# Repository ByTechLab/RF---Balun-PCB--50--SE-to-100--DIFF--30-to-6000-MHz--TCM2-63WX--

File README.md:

<div align="center">
    
</div>

Mini Circuits TCM2-63WX+ based balun PCB.

### Read more at BYTECHLAB:

<table style="width: 100%; border: none;" cellspacing="0" cellpadding="0" border="0">
  <tr>
    <td></td>
    <td>https://bytechlab.com/2025/07/balun-pcb-tcm2-63wx/</td>
  </tr>
</table>

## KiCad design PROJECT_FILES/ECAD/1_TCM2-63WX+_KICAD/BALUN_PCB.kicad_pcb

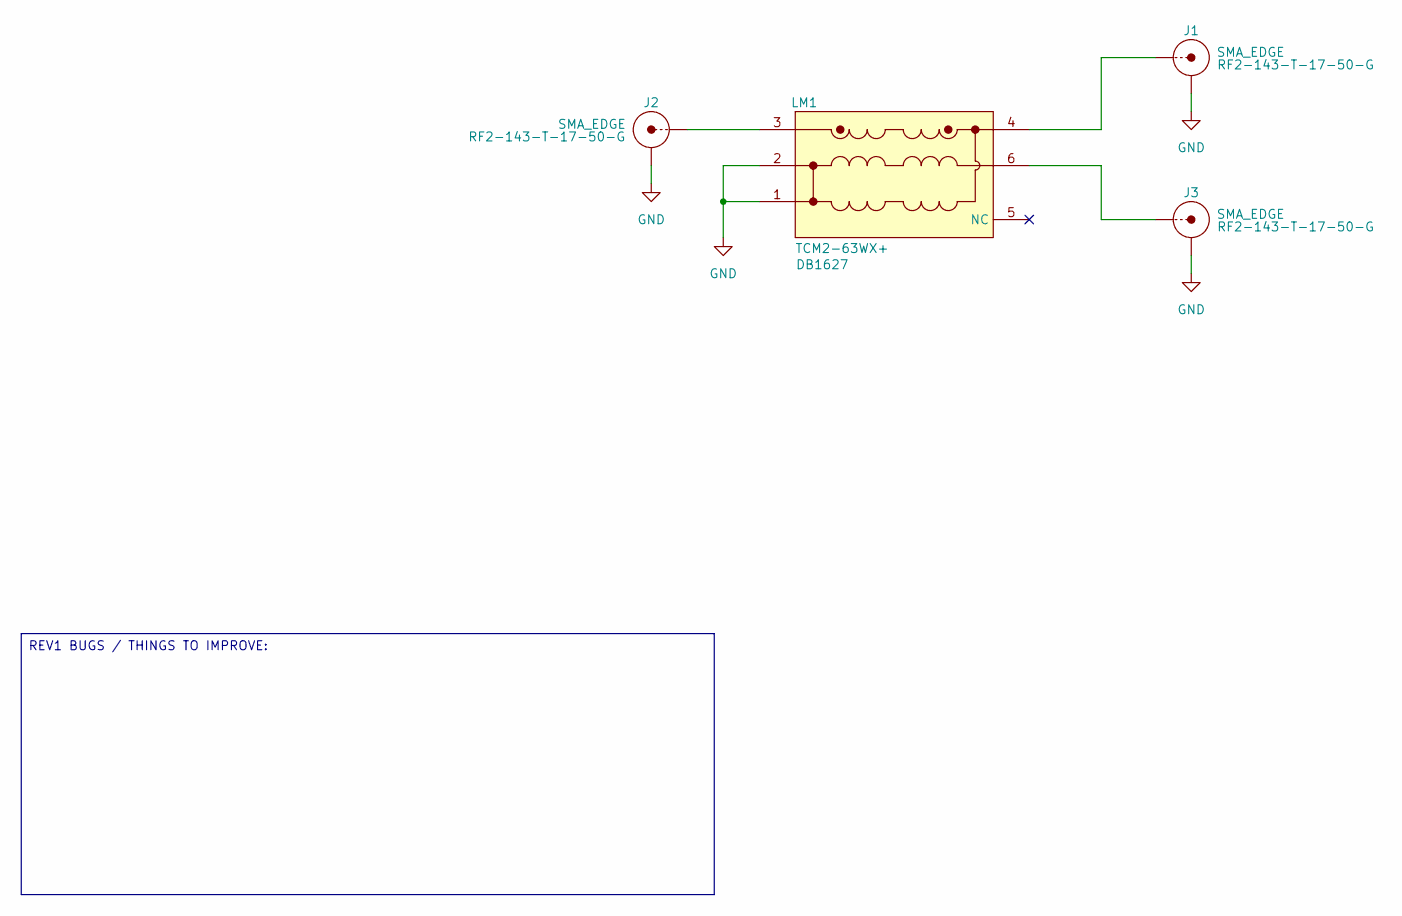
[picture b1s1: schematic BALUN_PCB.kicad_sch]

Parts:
J1, J2, J3: J_RF2-143-T-17-50-G; Manufacturer Part Number RF2-143-T-17-50-G
LM1: LM_TCM2-63WX+; Manufacturer Part Number TCM2-63WX+

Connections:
GND: J1.2 (GND), J2.2 (GND), J3.2 (GND), LM1.1, LM1.2
unnamed: J1.1 (SIG), LM1.4
unnamed: J2.1 (SIG), LM1.3
unnamed: J3.1 (SIG), LM1.6

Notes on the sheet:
REV1 BUGS / THINGS TO IMPROVE:

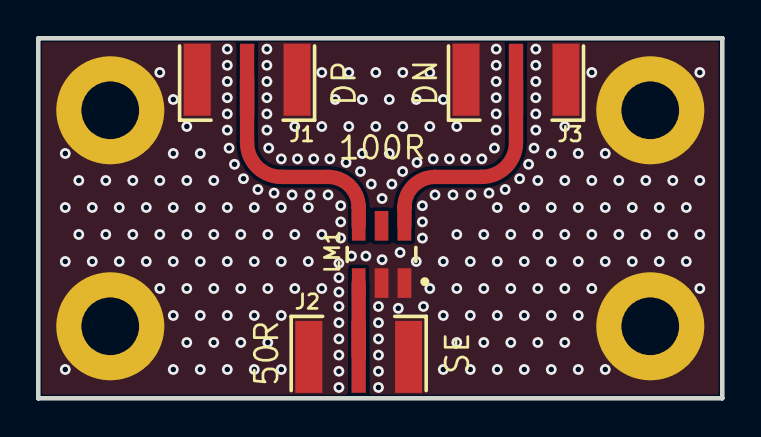
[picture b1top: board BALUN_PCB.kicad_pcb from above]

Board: 2 copper layers, 38.0 x 20.0 mm, 4 parts (0 on the bottom side), 4 nets.

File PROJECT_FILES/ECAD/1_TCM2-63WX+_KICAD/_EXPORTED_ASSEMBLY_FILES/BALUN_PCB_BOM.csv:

"Reference","Qty","Manufacturer","Manufacturer Part Number","SCH_FOOTPRINT"
"J1,J2,J3","3","Adam Tech","RF2-143-T-17-50-G","SMA_EDGE"
"LM1","1","MiniCircuits","TCM2-63WX+","DB1627"

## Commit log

2025-08-17 Uplaod files
